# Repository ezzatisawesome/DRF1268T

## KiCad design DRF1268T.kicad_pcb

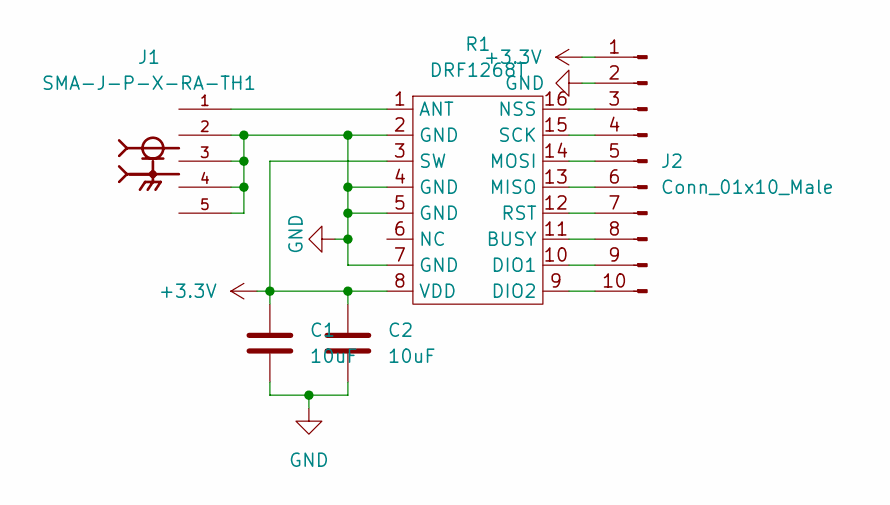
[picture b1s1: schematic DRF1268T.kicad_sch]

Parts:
C1, C2: 10uF; C_0201_0603Metric_Pad0.64x0.40mm_HandSolder
J1: SMA-J-P-X-RA-TH1; SAMTEC_SMA-J-P-X-RA-TH1; PARTREV K
J2: Conn_01x10_Male; PinSocket_1x10_P2.54mm_Vertical
R1: DRF1268T

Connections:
+3.3V: C1.1, C2.1, J2.1, R1.3 (SW), R1.8 (VDD)
GND: C1.2, C2.2, J1.2, J1.3, J1.4, J1.5, J2.2, R1.2 (GND), R1.4 (GND), R1.5 (GND), R1.7 (GND)
unnamed: J1.1, R1.1 (ANT)
unnamed: J2.10, R1.9 (DIO2)
unnamed: J2.9, R1.10 (DIO1)
unnamed: J2.8, R1.11 (BUSY)
unnamed: J2.7, R1.12 (RST)
unnamed: J2.6, R1.13 (MISO)
unnamed: J2.5, R1.14 (MOSI)
unnamed: J2.4, R1.15 (SCK)
unnamed: J2.3, R1.16 (NSS)

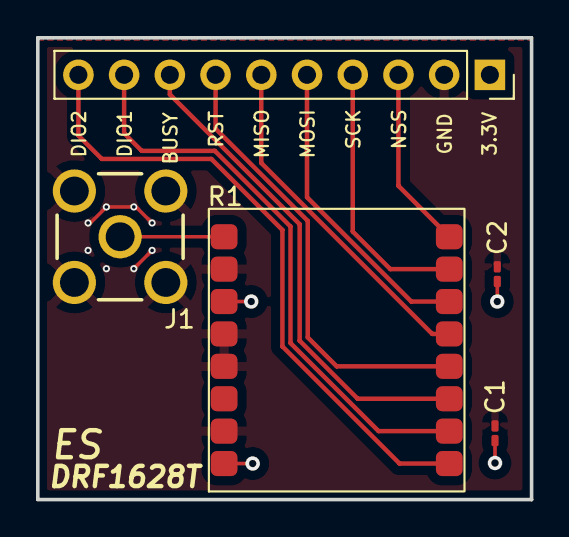
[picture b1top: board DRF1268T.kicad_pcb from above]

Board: 2 copper layers, 27.4 x 25.7 mm, 5 parts (0 on the bottom side), 11 nets.

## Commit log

2023-01-19 Check
2023-01-19 afasdf
2023-01-19 First draft
2023-01-21 Changes to pcb layout
2023-01-22 Changed
2023-02-01 edits
2023-02-01 Adding fab files
2023-02-02 Fixing model imports
